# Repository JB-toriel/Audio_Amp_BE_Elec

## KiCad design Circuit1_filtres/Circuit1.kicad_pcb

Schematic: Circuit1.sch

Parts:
C1, C2: 10u; C_1206_3216Metric_Pad1.42x1.75mm_HandSolder
C3: 1u; C_1206_3216Metric_Pad1.42x1.75mm_HandSolder
C4, C6: 10n; C_1206_3216Metric_Pad1.42x1.75mm_HandSolder
C5, C8: 1n; C_1206_3216Metric_Pad1.42x1.75mm_HandSolder
C7: 100n; C_1206_3216Metric_Pad1.42x1.75mm_HandSolder
J1: AudioJack3_Ground; Jack_3.5mm_PJ320D_Horizontal
J2: Conn_01x02_Female; PinHeader_1x02_P2.54mm_Vertical
J3: Conn_01x03_Female; PinHeader_1x03_P2.54mm_Vertical
R1, R2: 100k; R_1206_3216Metric_Pad1.42x1.75mm_HandSolder
R3, R6: 1k; R_1206_3216Metric_Pad1.42x1.75mm_HandSolder
R4, R9: 8.2k; R_1206_3216Metric_Pad1.42x1.75mm_HandSolder
R5: 3.9; R_1206_3216Metric_Pad1.42x1.75mm_HandSolder
R8: 3.9k; R_1206_3216Metric_Pad1.42x1.75mm_HandSolder
R10, R11: 39k; R_1206_3216Metric_Pad1.42x1.75mm_HandSolder
R13: 0; R_1206_3216Metric_Pad1.42x1.75mm_HandSolder
RV1, RV2, RV3: 10k; Potentiometer_Vishay_TS53YL_Vertical
Rpont1, Rpont2: 100k; R_1206_3216Metric_Pad1.42x1.75mm_HandSolder
U1: TSV912IDT; SOIC-8_3.9x4.9mm_P1.27mm
Ufiltre1: TSV912IDT; SOIC-8_3.9x4.9mm_P1.27mm
Ufiltrebis1: TSV912IDT; SOIC-8_3.9x4.9mm_P1.27mm

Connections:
GND: J1.S, J2.2, J3.2, Rpont2.1, U1.4 (V-), Ufiltre1.4 (V-), Ufiltrebis1.4 (V-)
unnamed: C1.1, R1.2
unnamed: C1.2, J1.R
unnamed: C2.1, R2.2
unnamed: C2.2, J1.T
unnamed: C3.1, C6.2, R10.2, Ufiltrebis1.2 (-)
unnamed: C3.2, R4.1
unnamed: C4.1, C5.2, R9.2, Ufiltre1.2 (-)
unnamed: C4.2, R5.1
unnamed: C5.1, R9.1, RV1.1, RV1.2, Ufiltre1.1
unnamed: C6.1, R10.1, RV2.2, RV2.3, Ufiltrebis1.1
unnamed: C7.1, C8.2, R11.2, Ufiltre1.6 (-)
unnamed: C7.2, R8.1
unnamed: C8.1, R11.1, RV3.1, RV3.2, Ufiltre1.7
unnamed: J3.1, R6.1, U1.7
unnamed: R1.1, R2.1, R3.2, U1.2 (-)
unnamed: R6.2, RV1.3, RV2.1, RV3.3, U1.6 (-)
unnamed: R4.2, R5.2, R8.2, R13.1
unnamed: R3.1, R13.2, U1.1
VCC: J2.1, J3.3, Rpont1.2, U1.8 (V+), Ufiltre1.8 (V+), Ufiltrebis1.8 (V+)
Vcc:2: Rpont1.1, Rpont2.2, U1.3 (+), U1.5 (+), Ufiltre1.3 (+), Ufiltre1.5 (+), Ufiltrebis1.3 (+)

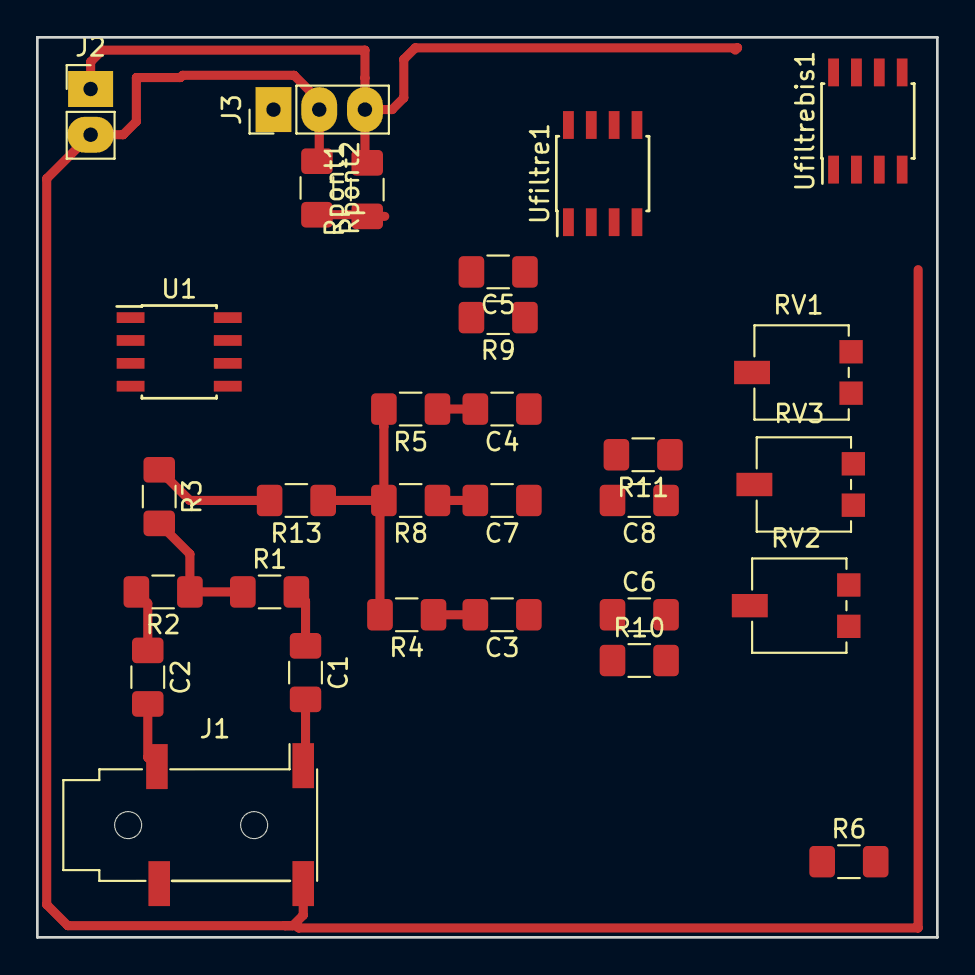
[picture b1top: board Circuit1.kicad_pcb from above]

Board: 2 copper layers, 50.0 x 50.0 mm, 30 parts (0 on the bottom side), 21 nets.
